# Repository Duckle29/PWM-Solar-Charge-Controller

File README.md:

# PWM-Solar-Charge-Controller

I have decided to revive this project again. It's gonna be brought back as the PWM10, as It'll be designed to handle 10A, which is a little over a 140W panel.
The Rev2 files are designed using KiCAD

This is an attempt at making an Arduino powered PWM solar charge controller.

The design of this controller is heavily based on Julian Iletts PWM5 controller, which he sadly discontinued.
He however makes some interesting Youtube videos.

  * [Website](http://256.co.uk)
  * [Yoututbe](https://www.youtube.com/user/julius256)

This is **not** done, and there is no protection added to the board as of yet.
This first revision is simply as complete as I could make it, before my patience ran out for that day.
I might very well add the last few bits and bops within a few days.

### No Firmware has been written for this board as of yet
And as such, features and implementations of the hardware has yet to be decided.

### What is special about this spin-off of the PWM5?
This board is:
  * Entirely Arduino compatible, as it uses an ATMega328P
  * Able to measure the voltage of *both* the battery and panel, allowing for alternative control algorithms
  * Fitted with a slot for an NRF24L01+ Transceiver, for sending all available data back and forth / control the PWM charge controller. (After flashing the boot-loader, the solder bridges should be shorted for this feature)
  * Fitted with an RGB LED, that can be controlled to display all sorts of different color combinations and patterns
  * Designed to be cheaply mass produced, with purely SMT parts except for the headers for ISP, NRF and FTDI.

### What needs to be done?
The following things need to be added:
  * Reverse polarity protection
  * Short circuit protection
  * A thorough check of the schematic and board. I slapped this together in one 8 hour sitting, so I'm bound to have missed something / messed something up
  * Firmware needs to be written
  * It needs to be tested in general.
  * Parts need to be checked for availability and pricing. If none are available in the used footprint, a substitute has to be found.

### Additional notes
If I decide the board is ready to go, I will order some assembled boards. If people are interested in some assembled boards, then comment in the issue that I opened for that purpose. I might order some home and send them to you for the price it cost me, and nothing more (that's assembled board cost + shipping)

### Renders:

Greetings!

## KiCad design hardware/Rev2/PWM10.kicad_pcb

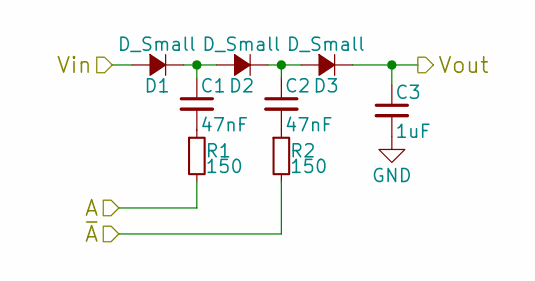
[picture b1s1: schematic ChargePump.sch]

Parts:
C1, C2: 47nF; C_0805_HandSoldering
C3: 1uF; C_0805_HandSoldering
D1, D2, D3: D_Small; D_SOD-123
R1, R2: 150; R_0603_HandSoldering

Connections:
+BATT: D1.2 (A); also elsewhere on the board
/PowerSwitching/GATEVCC: C3.1, D3.1 (K); also elsewhere on the board
A_N: R2.2; also elsewhere on the board
A_P: R1.2; also elsewhere on the board
GND: C3.2; also elsewhere on the board
unnamed: C1.1, D1.1 (K), D2.2 (A)
unnamed: C1.2, R1.1
unnamed: C2.1, D2.1 (K), D3.2 (A)
unnamed: C2.2, R2.1

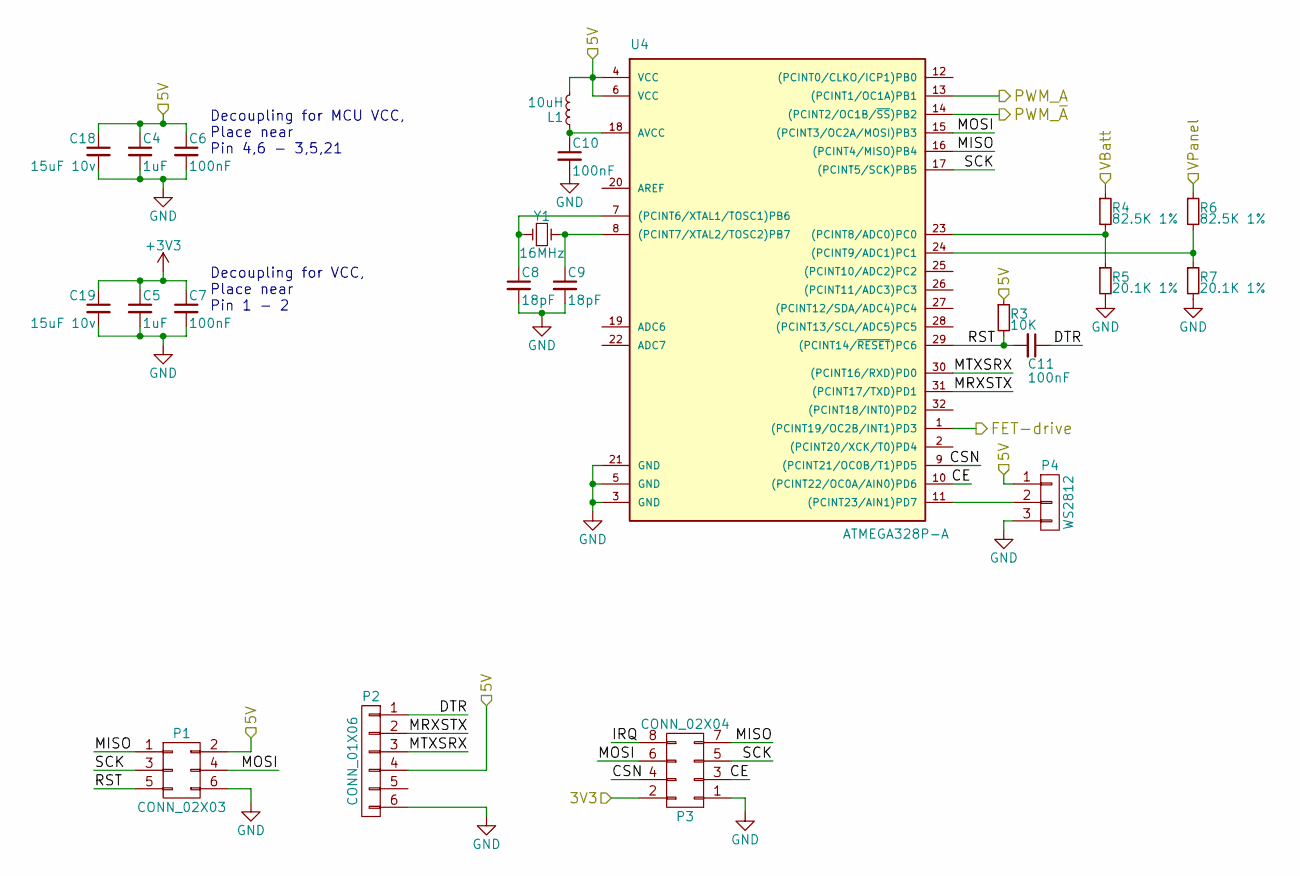
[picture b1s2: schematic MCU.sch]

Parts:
C4, C5: 1uF; C_0805_HandSoldering
C6, C7, C10, C11: 100nF; C_0805_HandSoldering
C8, C9: 18pF; C_0805_HandSoldering
C18, C19: 15uF 10v; C_1206_HandSoldering
L1: 10uH; R_1210_HandSoldering
P1: CONN_02X03; Pin_Header_Straight_2x03_Pitch2.54mm
P2: CONN_01X06; Pin_Header_Angled_1x06_Pitch2.54mm
P3: CONN_02X04; Pin_Header_Straight_2x04_Pitch2.54mm
P4: WS2812; Pin_Header_Angled_1x03_Pitch2.54mm
R3: 10K; R_0603_HandSoldering
R4, R6: 82.5K 1%; R_0603_HandSoldering
R5, R7: 20.1K 1%; R_0603_HandSoldering
U4: ATMEGA328P-A; TQFP-32_7x7mm_Pitch0.8mm
Y1: 16MHz; Crystal_SMD_HC49-SD

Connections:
+3V3: C5.1, C7.1, C19.1, P3.2; also elsewhere on the board
+5V: C4.1, C6.1, C18.1, L1.2, P1.2, P2.4, P4.1, R3.1, U4.4 (VCC), U4.6 (VCC); also elsewhere on the board
+BATT: R4.1; also elsewhere on the board
/MCU/CE: P3.3, U4.10 ((PCINT22/OC0A/AIN0)PD6)
/MCU/CSN: P3.4, U4.9 ((PCINT21/OC0B/T1)PD5)
/MCU/DTR: C11.1, P2.1
/MCU/FET-drive: U4.1 ((PCINT19/OC2B/INT1)PD3); also elsewhere on the board
/MCU/IRQ: P3.8
/MCU/MISO: P1.1, P3.7, U4.16 ((PCINT4/MISO)PB4)
/MCU/MOSI: P1.4, P3.6, U4.15 ((PCINT3/OC2A/MOSI)PB3)
/MCU/MRXSTX: P2.2, U4.31 ((PCINT17/TXD)PD1)
/MCU/MTXSRX: P2.3, U4.30 ((PCINT16/RXD)PD0)
/MCU/RST: C11.2, P1.5, R3.2, U4.29 ((PCINT14/~RESET~)PC6)
/MCU/SCK: P1.3, P3.5, U4.17 ((PCINT5/SCK)PB5)
A_N: U4.14 ((PCINT2/OC1B/~SS~)PB2); also elsewhere on the board
A_P: U4.13 ((PCINT1/OC1A)PB1); also elsewhere on the board
GND: C4.2, C5.2, C6.2, C7.2, C8.2, C9.2, C10.2, C18.2, C19.2, P1.6, P2.6, P3.1, P4.3, R5.2, R7.2, U4.3 (GND), U4.5 (GND), U4.21 (GND); also elsewhere on the board
unnamed: C8.1, U4.7 ((PCINT6/XTAL1/TOSC1)PB6), Y1.1
unnamed: C9.1, U4.8 ((PCINT7/XTAL2/TOSC2)PB7), Y1.2
unnamed: C10.1, L1.1, U4.18 (AVCC)
unnamed: P4.2, U4.11 ((PCINT23/AIN1)PD7)
unnamed: R4.2, R5.1, U4.23 ((PCINT8/ADC0)PC0)
unnamed: R6.2, R7.1, U4.24 ((PCINT9/ADC1)PC1)
VPP: R6.1; also elsewhere on the board

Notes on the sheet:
Decoupling for MCU VCC, Place near Pin 4,6 - 3,5,21
Decoupling for VCC, Place near Pin 1 - 2

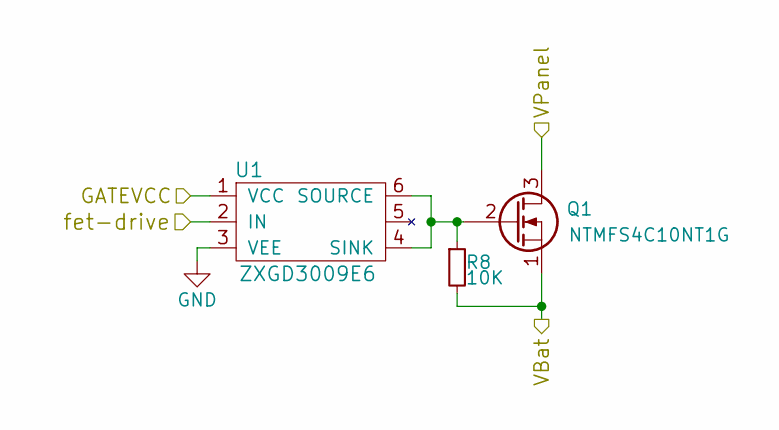
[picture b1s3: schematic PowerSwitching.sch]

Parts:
Q1: NTMFS4C10NT1G; PG-TDSON-8
R8: 10K; R_0603_HandSoldering
U1: ZXGD3009E6; SOT-363_SC-70-6_Handsoldering

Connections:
+BATT: Q1.1 (S), R8.2; also elsewhere on the board
/MCU/FET-drive: U1.2 (IN); also elsewhere on the board
/PowerSwitching/GATEVCC: U1.1 (VCC); also elsewhere on the board
GND: U1.3 (VEE); also elsewhere on the board
unnamed: Q1.2 (G), R8.1, U1.4 (SINK), U1.6 (SOURCE)
VPP: Q1.3 (D); also elsewhere on the board

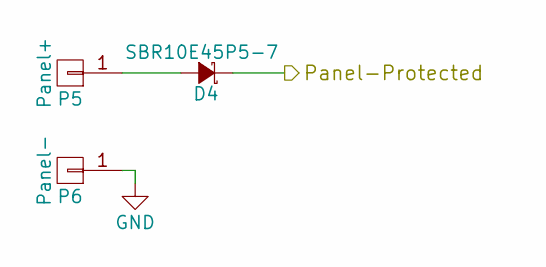
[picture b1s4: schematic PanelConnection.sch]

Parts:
D4: SBR10E45P5-7; PowerDI5
P5: Panel+; MountingHole_3.2mm_M3_Pad_Via
P6: Panel-; MountingHole_3.2mm_M3_Pad_Via

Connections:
GND: P6.1; also elsewhere on the board
unnamed: D4.2 (A), P5.1
VPP: D4.1 (K); also elsewhere on the board

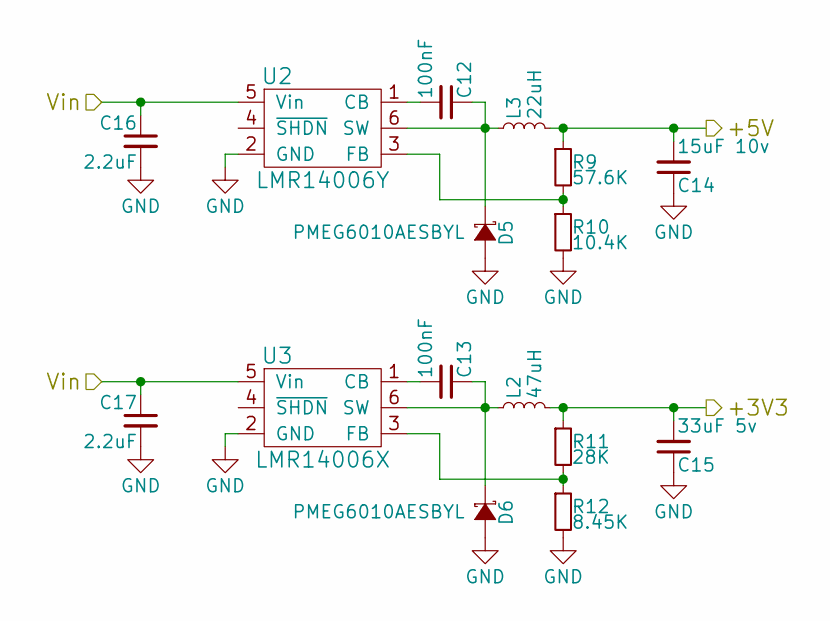
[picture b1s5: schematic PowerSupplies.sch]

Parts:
C12, C13: 100nF; C_0805_HandSoldering
C14: 15uF 10v; C_1206_HandSoldering
C15: 33uF 5v; C_1206_HandSoldering
C16, C17: 2.2uF; C_0805_HandSoldering
D5, D6: PMEG6010AESBYL; SOD-993
L2: 47uH; R_1210_HandSoldering; Part CBC3225T470MR
L3: 22uH; R_1210_HandSoldering; Part CBC3225T220MR
R9: 57.6K; R_0603_HandSoldering
R10: 10.4K; R_0603_HandSoldering
R11: 28K; R_0603_HandSoldering
R12: 8.45K; R_0603_HandSoldering
U2: LMR14006Y; TSOT-23-6_MK06A_HandSoldering
U3: LMR14006X; TSOT-23-6_MK06A_HandSoldering

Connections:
+3V3: C15.2, L2.2, R11.1; also elsewhere on the board
+5V: C14.2, L3.2, R9.1; also elsewhere on the board
GND: C14.1, C15.1, C16.2, C17.2, D5.2 (A), D6.2 (A), R10.2, R12.2, U2.2 (GND), U3.2 (GND); also elsewhere on the board
unnamed: C12.1, D5.1 (K), L3.1, U2.6 (SW)
unnamed: C12.2, U2.1 (CB)
unnamed: C13.1, D6.1 (K), L2.1, U3.6 (SW)
unnamed: C13.2, U3.1 (CB)
unnamed: R9.2, R10.1, U2.3 (FB)
unnamed: R11.2, R12.1, U3.3 (FB)
VPP: C16.1, C17.1, U2.5 (Vin), U3.5 (Vin); also elsewhere on the board

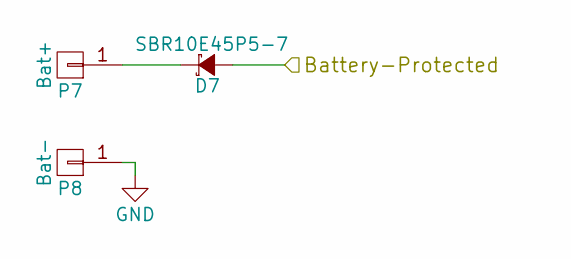
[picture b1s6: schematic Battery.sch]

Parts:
D7: SBR10E45P5-7; PowerDI5
P7: Bat+; MountingHole_3.2mm_M3_Pad_Via
P8: Bat-; MountingHole_3.2mm_M3_Pad_Via

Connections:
+BATT: D7.2 (A); also elsewhere on the board
GND: P8.1; also elsewhere on the board
unnamed: D7.1 (K), P7.1

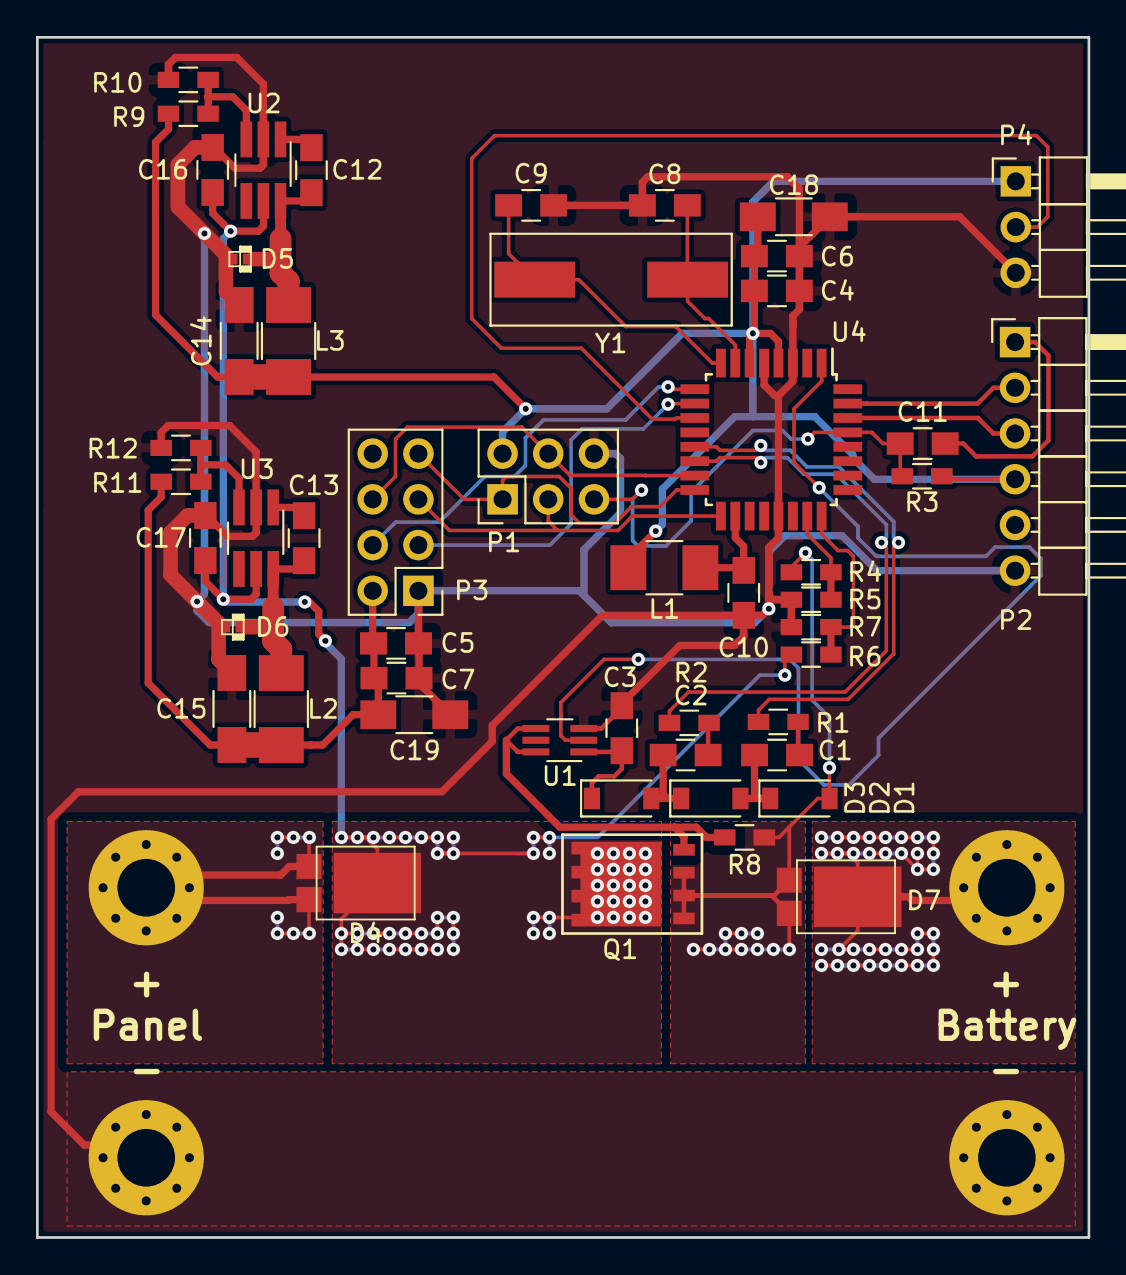
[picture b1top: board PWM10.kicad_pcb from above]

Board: 2 copper layers, 58.4 x 66.7 mm, 55 parts (0 on the bottom side), 37 nets.

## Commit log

2015-04-15 Added charge pump for v-gate
2015-04-15 Schematic pre-finished. Needs values added
2015-04-15 Board laid out
2015-04-15 Fixing LDO input pin
2015-04-15 Added copper pour, sorted silk screen
2015-04-15 Added PDF of both schematic and board
2015-04-15 Added dimentions to the board
2015-04-15 Wrote the readme
2015-04-15 Correct Julians last name. Sorry
2015-04-15 Added MIT License
2015-04-15 Corrected some erros in the readme
2015-04-15 Made a hardware and firmware folder
2015-04-15 Propperly filtered AVCC
2015-04-15 Fixed copper ground pour
2015-04-15 Updated PDF files to reflect latest commits
2017-05-23 Finished schematic of Rev2
2017-05-23 doing some stupid shit to rename rev1
2017-05-23 Renamed rev1 to Rev1
2017-05-29 created PCB and gerbers
2017-05-29 Added renders
2017-05-29 Added renders to readme. Let's see how huge they are
